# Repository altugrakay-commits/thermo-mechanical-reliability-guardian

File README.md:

# 🛡️ Thermo-Mechanical Reliability Guardian

An automated, physics-informed DevSecOps agent that predicts thermal fatigue life in 2.5D/3D packaging. Built for the **GitLab Transcend Hackathon 2026** (Showcase Track).

## 📖 Overview

In modern hardware development, software and hardware design are siloed. When a developer commits a change to a PCB layout, there is no automated way to check if that change will cause a thermo-mechanical failure (like solder joint fatigue) in the real world. Physical prototypes must be built and tested — a slow and expensive process.

The **Thermo-Mechanical Reliability Guardian** bridges this gap. It acts as an automated CI/CD agent that:
1.  **Parses real ECAD files** (KiCad `.kicad_pcb` and Gerber copper layers).
2.  **Runs non-linear thermal fatigue simulations** using the Darveaux and Norris-Landzberg models.
3.  **Posts the results** directly back to the GitLab Merge Request workflow.
4.  **Visualizes the thermal strain distribution** across every pad on the board.

**Figure 1:** Live analysis of a 106-pad Top Copper layer, with color-coded fatigue life per pad.

## 🚀 Key Features

-   **Multi-Format ECAD Parsing:** Directly reads KiCad PCB files and Gerber copper layers (`.gtl`, `.gbl`, `.gts`, `.gbs`) using `kiutils` and `gerbonara`.
-   **Per-Pad Physics Simulation:** Calculates thermal fatigue life for every individual pad on the board, not just a single average.
-   **Real-Time Risk Assessment:** Identifies the critical pad (worst-case cycles to failure) and reports a clear `PASS` or `WARNING` status.
-   **Interactive 3D Dashboard:** A Streamlit + PyVista web app that renders the board layout with color-coded fatigue life per pad.
-   **GitLab CI/CD Integration:** Automatically triggers on Merge Requests that modify `.kicad_pcb`, `.gtl`, `.gbl`, `.gts`, `.gbs`, or `design_config.json` files.

## 🏗️ Architecture

The project is modularized into four core components:

| File | Role | Description |
|------|------|-------------|
| **`parser.py`** | Input | Reads `.kicad_pcb`, `.gbr`/`.gtl`/`.gbl`/etc., or `.json`. Extracts pad geometry (position, size, shape). |
| **`physics_engine.py`** | Processing | Core mathematical engine. Runs Darveaux and Norris-Landzberg models per-pad. |
| **`agent.py`** | DevSecOps | CI/CD agent. Parses the design, runs the engine, and posts results to a GitLab Merge Request. |
| **`app.py`** | Visualization | Streamlit dashboard for interactive exploration and 3D visualization. |

## 🛠️ Tech Stack

-   **Language:** Python 3.9+
-   **Numerical Modeling:** NumPy
-   **Web Framework:** Streamlit
-   **3D Visualization:** PyVista
-   **ECAD Parsing:** `kiutils` (KiCad), `gerbonara` (Gerber)
-   **DevSecOps:** GitLab CI/CD, `python-gitlab` API

## 💻 Local Setup & Installation

1.  **Clone the repository:**
    ```bash
    git clone https://gitlab.com/akay7592941/thermo-mechanical-reliability-guardian.git
    
    cd thermo-mechanical-reliability-guardian
    ```
2. **Install dependencies:**
    ```bash
    pip install -r requirements.txt
    ```
3. **Run the interactive Dashboard:**
   ```bash
   streamlit run app.py
   ```
   This will open a browser window at `http://localhost:8501` where you can tweak parameters and view the 3D thermal strain visualizations.

4. **Run the CI Agent Locally (Simulation):**
   ```bash
   python agent.py
   ```
   Note: To post comments back to GitLab, ensure the `GITLAB_TOKEN` environment is set.

## 📊 Example Output
The agent generates a report like this upon running:

  **🛡️ Thermo-Mechanical Reliability Report**
 - **Pads Analyzed:** 106
 - **Worst-Case Darveaux Cycles:** 892,638
 - **Norris-Landzberg Cycles:** 14,165
 - **Status:** PASS
 - **Critical Pad Location:** X = 5.00mm, Y = -23.00mm (Ø0.50mm)

## 📂 Supported File Formats
| Format | Extension | Best For |
|------|------|-------------|
| KiCad PCB | `.kicad_pcb` | Full board with component pads |
| Gerber Top Copper | `.gtl` | Via arrays and copper features |
| Gerber Bottom Copper | `.gbl` | Bottom-layer pads |
| Gerber Top Solder Mask | `.gts` | Solder mask openings |
| Gerber Bottom Solder Mask | `.gbs` | Bottom solder mask openings |
| JSON Config | `.json` | Manual parameter entry |

**Note:** Layers like `.gto` (silkscreen) or `.gm1` (edge cuts) do not contain pads and will display a warning. Use copper or solder mask layers for accurate results.

## 🔮 Future Work
 - **Full 3D FEA Integration:** Replace empirical models with a full Finite Element Analysis solver (e.g., FEniCS, CalculiX) for non-linear creep/plasticity.
 - **GitLab Orbit Integration:** Query the Orbit knowledge graph to correlate design changes with historical failure data.
 - **Automated Layer Stackup Extraction:** Read material properties directly from the KiCad stackup instead of using defaults.

## 📜 License
This project is licensed under the MIT License - see the [LICENSE](LICENSE.md) file for details.

## 🙏 Acknowledgments
 - Built for the **GitLab Transcend Hackathon 2026.**
 - Physics models based on standard reliability engineering literature (Darveaux, Norris-Landzberg).
 - Developed by **Altug Remzi Akay, Ph.D.**

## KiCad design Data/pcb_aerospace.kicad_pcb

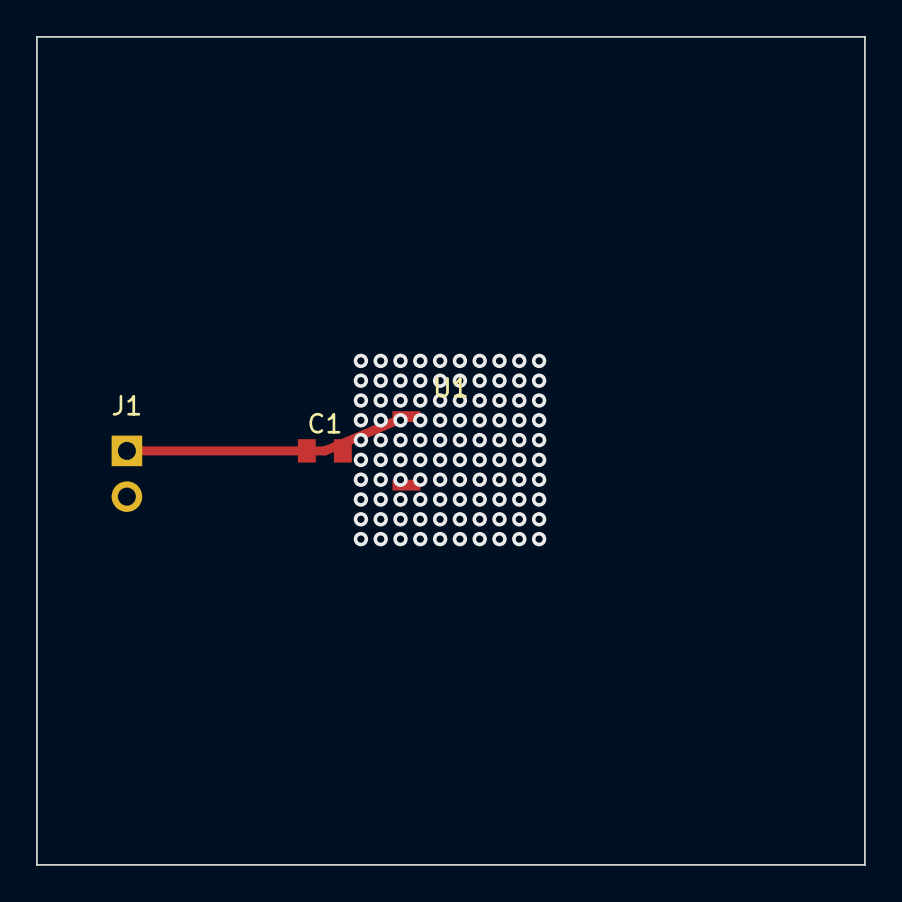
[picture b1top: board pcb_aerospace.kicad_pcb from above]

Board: 2 copper layers, 46.0 x 46.0 mm, 3 parts (0 on the bottom side), 2 nets.

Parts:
C1: 100nF; C_0805_2012Metric
J1: Power_In; PinHeader_1x02_P2.54mm_Vertical
U1: IC; SOIC-8_3.9x4.9mm_P1.27mm

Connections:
GND: C1.2, J1.2, U1.4
VCC: C1.1, J1.1, U1.1

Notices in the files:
README.md:
License: MIT
